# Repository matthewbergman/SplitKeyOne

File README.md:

# SplitKeyOne
Very simple split keyboard PCB layout and firmware using Cherry MX switches and Teensy3 micro.

### CAD
KiCAD pcb files

TODO:
* Fix the stabalizer mounting holes for vertically mounted keycaps
* Add more mounting holes for rigidity
* Switch to SMT diodes or switches with built in diodes

### SplitKeyOneFirmware
Simple firmware to read the key matrix and send the correct keypress or keyrelease signal. Optionally lights up the LED for each key while it is pressed.

TODO:
* Emulate mouse buttons
* Emulate joystick axis and buttons

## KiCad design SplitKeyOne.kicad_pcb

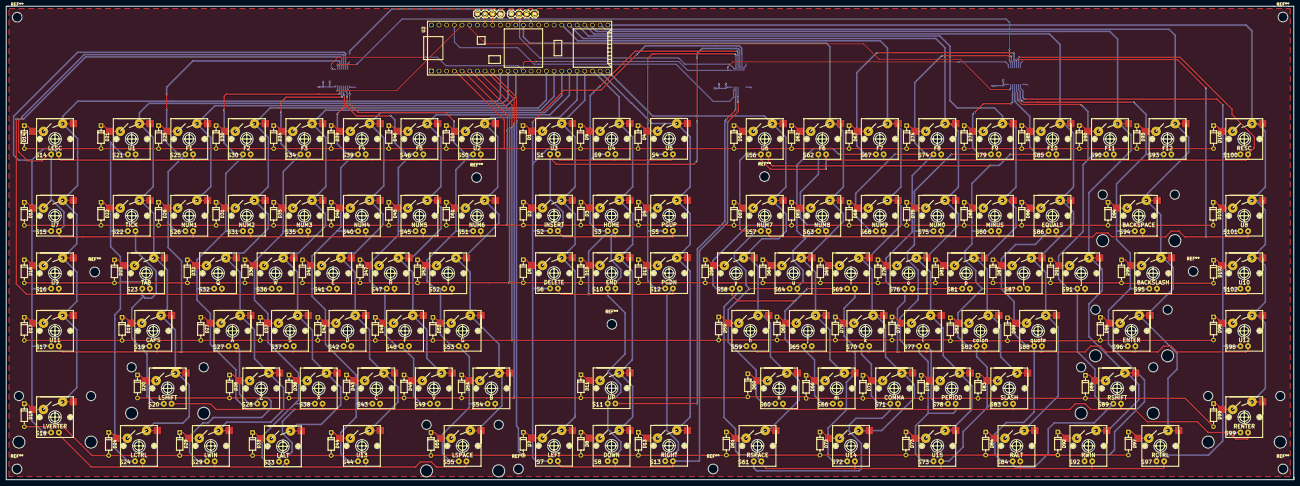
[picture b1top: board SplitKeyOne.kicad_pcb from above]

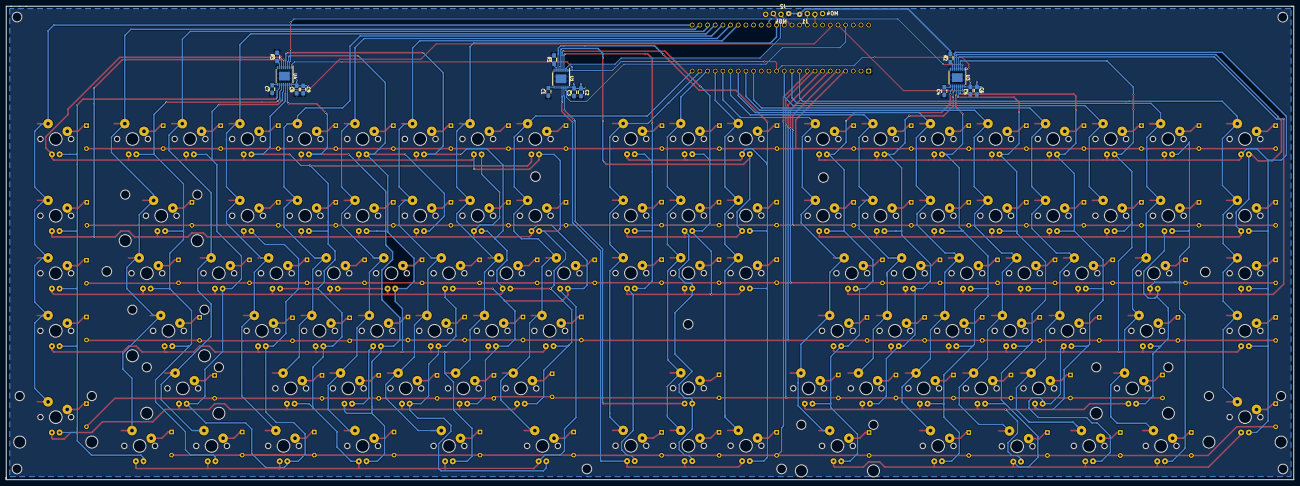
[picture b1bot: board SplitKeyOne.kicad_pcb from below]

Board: 2 copper layers, 426.2 x 156.7 mm, 222 parts (15 on the bottom side), 169 nets.

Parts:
C1, C4: 27pF; C_0805_HandSoldering
C2, C5, C8: 22uF; C_0805_HandSoldering
C3, C6, C9: 0.1uF; C_0805_HandSoldering
C7: C; C_0805_HandSoldering
D1, D2, D3, D4, D5, D6, D7, D8, D9, D10, D11, D12, D13, D14, D15, D16, D17, D18, D19, D20, D21, D22, D23, D24, D25, D26, D27, D28, D29, D30, D31, D32, D33, D34, D35, D36, D37, D38, D39, D40, D41, D42, D43, D44, D45, D46, D47, D48, D49, D50, D51, D52, D53, D54, D55, D56, D57, D58, D59, D60, D61, D62, D63, D64, D65, D66, D67, D68, D69, D70, D71, D72, D73, D74, D75, D76, D77, D78, D79, D80, D81, D82, D83, D84, D85, D86, D87, D88, D89, D90, D91, D92, D93, D94, D95, D96, D97, D98, D99, D100, D101, D102: D; D_DO-35_SOD27_P7.62mm_Horizontal
J1, J2: M04; SparkFun-1X04_LOCK
R1, R3: 56k; R_0805_HandSoldering
R2: 56K; R_0805_HandSoldering
S1: U3; CHERRY-MX-LED-Socket
S2: INSERT; CHERRY-MX-LED-Socket
S3: HOME; CHERRY-MX-LED-Socket
S4: U5; CHERRY-MX-LED-Socket
S5: PGUP; CHERRY-MX-LED-Socket
S6: DELETE; CHERRY-MX-LED-Socket
S7: LEFT; CHERRY-MX-LED-Socket
S8: DOWN; CHERRY-MX-LED-Socket
S9: U4; CHERRY-MX-LED-Socket
S10: END; CHERRY-MX-LED-Socket
S11: UP; CHERRY-MX-LED-Socket
S12: PGDN; CHERRY-MX-LED-Socket
S13: RIGHT; CHERRY-MX-LED-Socket
S14: LESC; CHERRY-MX-LED-Socket
S15: U7; CHERRY-MX-LED-Socket
S16: U9; CHERRY-MX-LED-Socket
S17: U11; CHERRY-MX-LED-Socket
S18: LVENTER; CHERRY-MX-LED-Socket-2-stabilizer
S19: CAPS; CHERRY-MX-LED-Socket
S20: LSHIFT; CHERRY-MX-LED-Socket-2-stabilizer
S21: U1; CHERRY-MX-LED-Socket
S22: TICK; CHERRY-MX-LED-Socket
S23: TAB; CHERRY-MX-LED-Socket
S24: LCTRL; CHERRY-MX-LED-Socket
S25: F1; CHERRY-MX-LED-Socket
S26: NUM1; CHERRY-MX-LED-Socket
S27: A; CHERRY-MX-LED-Socket
S28: Z; CHERRY-MX-LED-Socket
S29: LWIN; CHERRY-MX-LED-Socket
S30: F2; CHERRY-MX-LED-Socket
S31: NUM2; CHERRY-MX-LED-Socket
S32: Q; CHERRY-MX-LED-Socket
S33: LALT; CHERRY-MX-LED-Socket
S34: F3; CHERRY-MX-LED-Socket
S35: NUM3; CHERRY-MX-LED-Socket
S36: W; CHERRY-MX-LED-Socket
S37: S; CHERRY-MX-LED-Socket
S38: X; CHERRY-MX-LED-Socket
S39: F4; CHERRY-MX-LED-Socket
S40: NUM4; CHERRY-MX-LED-Socket
S41: E; CHERRY-MX-LED-Socket
S42: D; CHERRY-MX-LED-Socket
S43: C; CHERRY-MX-LED-Socket
S44: U13; CHERRY-MX-LED-Socket
S45: NUM5; CHERRY-MX-LED-Socket
S46: F5; CHERRY-MX-LED-Socket
S47: R; CHERRY-MX-LED-Socket
S48: F; CHERRY-MX-LED-Socket
S49: V; CHERRY-MX-LED-Socket
S50: U2; CHERRY-MX-LED-Socket
S51: NUM6; CHERRY-MX-LED-Socket
S52: T; CHERRY-MX-LED-Socket
S53: G; CHERRY-MX-LED-Socket
S54: B; CHERRY-MX-LED-Socket
S55: LSPACE; CHERRY-MX-LED-Socket-2-stabilizer
S56: U6; CHERRY-MX-LED-Socket
S57: NUM7; CHERRY-MX-LED-Socket
S58: y; CHERRY-MX-LED-Socket
S59: h; CHERRY-MX-LED-Socket
S60: n; CHERRY-MX-LED-Socket
S61: RSPACE; CHERRY-MX-LED-Socket
S62: F6; CHERRY-MX-LED-Socket
S63: NUM8; CHERRY-MX-LED-Socket
S64: u; CHERRY-MX-LED-Socket
S65: j; CHERRY-MX-LED-Socket
S66: m; CHERRY-MX-LED-Socket
S67: F7; CHERRY-MX-LED-Socket
S68: NUM9; CHERRY-MX-LED-Socket
S69: i; CHERRY-MX-LED-Socket
S70: k; CHERRY-MX-LED-Socket
S71: COMMA; CHERRY-MX-LED-Socket
S72: U14; CHERRY-MX-LED-Socket
S73: U15; CHERRY-MX-LED-Socket
S74: F8; CHERRY-MX-LED-Socket
S75: NUM0; CHERRY-MX-LED-Socket
S76: o; CHERRY-MX-LED-Socket
S77: l; CHERRY-MX-LED-Socket
S78: PERIOD; CHERRY-MX-LED-Socket
S79: F9; CHERRY-MX-LED-Socket
S80: MINUS; CHERRY-MX-LED-Socket
S81: p; CHERRY-MX-LED-Socket
S82: colon; CHERRY-MX-LED-Socket
S83: SLASH; CHERRY-MX-LED-Socket
S84: RALT; CHERRY-MX-LED-Socket
S85: F10; CHERRY-MX-LED-Socket
S86: EQUALS; CHERRY-MX-LED-Socket
S87: {; CHERRY-MX-LED-Socket
S88: quote; CHERRY-MX-LED-Socket
S89: RSHIFT; CHERRY-MX-LED-Socket-2-stabilizer
S90: F11; CHERRY-MX-LED-Socket
S91: ]; CHERRY-MX-LED-Socket
S92: RWIN; CHERRY-MX-LED-Socket
S93: F12; CHERRY-MX-LED-Socket
S94: BACKSPACE; CHERRY-MX-LED-Socket-2-stabilizer
S95: BACKSLASH; CHERRY-MX-LED-Socket
S96: ENTER; CHERRY-MX-LED-Socket-2-stabilizer
S97: RCTRL; CHERRY-MX-LED-Socket
S98: U12; CHERRY-MX-LED-Socket
S99: RENTER; CHERRY-MX-LED-Socket-2-stabilizer
S100: RESC; CHERRY-MX-LED-Socket
S101: U8; CHERRY-MX-LED-Socket
S102: U10; CHERRY-MX-LED-Socket
U1, U3, U4: MAX6951; TSSOP-16-1EP_4.4x5mm_Pitch0.65mm
U2: Teensy3.6_nopogo; Teensy35_36_nopogo

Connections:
5V: C2.1, C3.1, C5.1, C6.1, C8.1, C9.1, J1.4, J2.4, U1.16, U2.53, U3.16, U4.16
/C9: S1.S2, S2.S2, S6.S2, S7.S2, U2.21
/C10: S3.S2, S8.S2, S9.S2, S10.S2, S11.S2, U2.22
/C11: S4.S2, S5.S2, S12.S2, S13.S2, U2.23
/G15: J2.3, U2.42
/G16: J2.2, U2.43
/LED0: S1.K, S2.A, S4.K, S6.A, S7.A, S9.K, U1.6
/LED1: S1.A, S2.K, S3.K, S5.K, S8.A, S10.A, S11.A, U1.5
/LED2: S3.A, S6.K, S9.A, S10.K, S12.K, S13.A, U1.4
/LED3: S4.A, S5.A, S12.A, U1.3
/LED4: S11.K, U1.14
/LED5: S7.K, S8.K, S13.K, U1.13
/LED_CS1: U1.15, U2.50
/left/LED0: S14.K, S15.A, S16.A, S17.A, S18.A, S21.K, S25.K, S30.K, S34.K, S39.K, S46.K, S50.K, U3.6
/left/LED1: S14.A, S15.K, S19.A, S20.A, S22.K, S23.A, S26.K, S31.K, S35.K, S40.K, S45.K, S51.K, U3.5
/left/LED2: S16.K, S21.A, S22.A, S23.K, S24.A, S32.K, S36.K, S41.K, S47.K, S52.K, U3.4
/left/LED3: S17.K, S19.K, S25.A, S26.A, S27.K, S28.A, S29.A, S37.K, S42.K, S48.K, S53.K, U3.3
/left/LED4: S20.K, S27.A, S28.K, S30.A, S31.A, S32.A, S33.A, S38.K, S43.K, S49.K, S54.K, U3.14
/left/LED5: S18.K, S24.K, S29.K, S33.K, S34.A, S35.A, S36.A, S37.A, S38.A, S44.K, S55.K, U3.13
/left/LED6: S39.A, S40.A, S41.A, S42.A, S43.A, S44.A, U3.12
/left/LED7: S45.A, S46.A, S47.A, S48.A, S49.A, U3.11
/left/LED8: S50.A, S51.A, S52.A, S53.A, S54.A, S55.A, U3.10
/right/LED0: S56.A, S57.A, S59.A, S60.A, S62.K, S64.A, S67.K, S74.K, S79.K, S85.K, S90.K, S93.K, S100.K, U4.6
/right/LED1: S57.K, S58.A, S62.A, S63.K, S65.A, S66.A, S68.K, S69.A, S75.K, S80.K, S86.K, S94.K, S101.K, U4.5
/right/LED2: S61.A, S63.A, S64.K, S67.A, S69.K, S70.A, S71.A, S76.K, S81.K, S87.K, S91.K, S95.K, S102.K, U4.4
/right/LED3: S59.K, S65.K, S68.A, S70.K, S72.A, S74.A, S76.A, S77.K, S78.A, S82.K, S88.K, S96.K, S98.K, U4.3
/right/LED4: S60.K, S66.K, S71.K, S73.A, S75.A, S77.A, S78.K, S79.A, S81.A, S83.K, S89.K, S99.K, U4.14
/right/LED5: S56.K, S58.K, S61.K, S72.K, S73.K, S80.A, S82.A, S83.A, S84.K, S85.A, S87.A, S92.K, S97.K, U4.13
/right/LED6: S84.A, S86.A, S88.A, S89.A, S90.A, S91.A, U4.12
/right/LED7: S92.A, S93.A, S94.A, S95.A, S96.A, U4.11
/right/LED8: S97.A, S98.A, S99.A, S100.A, S101.A, S102.A, U4.10
C1: S14.S2, S15.S2, S16.S2, S17.S2, S18.S2, U2.10
C2: S19.S2, S20.S2, S21.S2, S22.S2, S23.S2, S24.S2, U2.11
C3: S25.S2, S26.S2, U2.12
C4: S27.S2, S28.S2, S29.S2, S30.S2, S31.S2, S32.S2, U2.16
C5: S33.S2, S34.S2, S35.S2, S36.S2, S37.S2, S38.S2, U2.17
C6: S39.S2, S40.S2, S41.S2, S42.S2, S43.S2, S44.S2, U2.18
C7: S45.S2, S46.S2, S47.S2, S48.S2, S49.S2, U2.19
C8: S50.S2, S51.S2, S52.S2, S53.S2, S54.S2, S55.S2, U2.20
C12: S56.S2, S57.S2, S58.S2, S59.S2, S60.S2, S61.S2, U2.24
C13: S62.S2, S63.S2, S64.S2, S65.S2, S66.S2, U2.41
C14: S67.S2, S68.S2, S69.S2, S70.S2, S71.S2, S72.S2, U2.36
C15: S73.S2, S74.S2, S75.S2, S76.S2, S77.S2, S78.S2, U2.35
C16: S79.S2, S80.S2, S81.S2, S82.S2, S83.S2, U2.34
C17: S84.S2, S85.S2, S86.S2, S87.S2, S88.S2, U2.33
C18: S89.S2, S90.S2, S91.S2, S92.S2, U2.32
C19: S93.S2, S94.S2, S95.S2, S96.S2, S97.S2, U2.31
C20: S98.S2, S99.S2, S100.S2, S101.S2, S102.S2, U2.30
GND: C1.2, C2.2, C3.2, C4.2, C5.2, C6.2, C7.2, C8.2, C9.2, J1.1, J2.1, R1.2, R2.2, R3.2, U1.8, U1.17, U2.1, U3.8, U3.17, U4.8, U4.17
LED_CS2: U2.49, U3.15
LED_CS3: U2.48, U4.15
MOSI: U1.1, U2.13, U3.1, U4.1
unnamed: C1.1, U1.9
unnamed: C4.1, U3.9
unnamed: C7.1, U4.9
unnamed: D1.1, S1.S1
unnamed: D2.1, S2.S1
unnamed: D3.1, S3.S1
unnamed: D4.1, S4.S1
unnamed: D5.1, S5.S1
unnamed: D6.1, S6.S1
unnamed: D7.1, S7.S1
unnamed: D8.1, S8.S1
unnamed: D9.1, S9.S1
unnamed: D10.1, S10.S1
unnamed: D11.1, S11.S1
unnamed: D12.1, S12.S1
unnamed: D13.1, S13.S1
unnamed: D14.1, S14.S1
unnamed: D15.1, S15.S1
unnamed: D16.1, S16.S1
unnamed: D17.1, S17.S1
unnamed: D18.1, S18.S1
unnamed: D19.1, S19.S1
unnamed: D20.1, S20.S1
unnamed: D21.1, S21.S1
unnamed: D22.1, S22.S1
unnamed: D23.1, S23.S1
unnamed: D24.1, S24.S1
unnamed: D25.1, S25.S1
unnamed: D26.1, S26.S1
unnamed: D27.1, S27.S1
unnamed: D28.1, S28.S1
unnamed: D29.1, S29.S1
unnamed: D30.1, S30.S1
unnamed: D31.1, S31.S1
unnamed: D32.1, S32.S1
unnamed: D33.1, S33.S1
unnamed: D34.1, S34.S1
unnamed: D35.1, S35.S1
unnamed: D36.1, S36.S1
unnamed: D37.1, S37.S1
unnamed: D38.1, S38.S1
unnamed: D39.1, S39.S1
unnamed: D40.1, S40.S1
unnamed: D41.1, S41.S1
unnamed: D42.1, S42.S1
unnamed: D43.1, S43.S1
unnamed: D44.1, S44.S1
unnamed: D45.1, S45.S1
unnamed: D46.1, S46.S1
unnamed: D47.1, S47.S1
unnamed: D48.1, S48.S1
unnamed: D49.1, S49.S1
unnamed: D50.1, S50.S1
unnamed: D51.1, S51.S1
unnamed: D52.1, S52.S1
unnamed: D53.1, S53.S1
unnamed: D54.1, S54.S1
unnamed: D55.1, S55.S1
unnamed: D56.1, S56.S1
unnamed: D57.1, S57.S1
unnamed: D58.1, S58.S1
unnamed: D59.1, S59.S1
unnamed: D60.1, S60.S1
unnamed: D61.1, S61.S1
unnamed: D62.1, S62.S1
unnamed: D63.1, S63.S1
unnamed: D64.1, S64.S1
unnamed: D65.1, S65.S1
unnamed: D66.1, S66.S1
unnamed: D67.1, S67.S1
unnamed: D68.1, S68.S1
unnamed: D69.1, S69.S1
unnamed: D70.1, S70.S1
unnamed: D71.1, S71.S1
unnamed: D72.1, S72.S1
unnamed: D73.1, S73.S1
unnamed: D74.1, S74.S1
unnamed: D75.1, S75.S1
unnamed: D76.1, S76.S1
unnamed: D77.1, S77.S1
unnamed: D78.1, S78.S1
unnamed: D79.1, S79.S1
unnamed: D80.1, S80.S1
unnamed: D81.1, S81.S1
unnamed: D82.1, S82.S1
unnamed: D83.1, S83.S1
unnamed: D84.1, S84.S1
unnamed: D85.1, S85.S1
unnamed: D86.1, S86.S1
unnamed: D87.1, S87.S1
unnamed: D88.1, S88.S1
unnamed: D89.1, S89.S1
unnamed: D90.1, S90.S1
unnamed: D91.1, S91.S1
unnamed: D92.1, S92.S1
unnamed: D93.1, S93.S1
unnamed: D94.1, S94.S1
unnamed: D95.1, S95.S1
unnamed: D96.1, S96.S1
unnamed: D97.1, S97.S1
unnamed: D98.1, S98.S1
unnamed: D99.1, S99.S1
unnamed: D100.1, S100.S1
unnamed: D101.1, S101.S1
unnamed: D102.1, S102.S1
unnamed: R1.1, U1.7
unnamed: R2.1, U3.7
unnamed: R3.1, U4.7
R1: D1.2, D4.2, D9.2, D14.2, D21.2, D25.2, D30.2, D34.2, D39.2, D46.2, D50.2, D56.2, D62.2, D67.2, D74.2, D79.2, D85.2, D90.2, D93.2, D100.2, U2.4
R2: D2.2, D3.2, D5.2, D15.2, D22.2, D26.2, D31.2, D35.2, D40.2, D45.2, D51.2, D57.2, D63.2, D68.2, D75.2, D80.2, D86.2, D94.2, D101.2, U2.5
R3: D6.2, D10.2, D12.2, D16.2, D23.2, D32.2, D36.2, D41.2, D47.2, D52.2, D58.2, D64.2, D69.2, D76.2, D81.2, D87.2, D91.2, D95.2, D102.2, U2.6
R4: D17.2, D19.2, D27.2, D37.2, D42.2, D48.2, D53.2, D59.2, D65.2, D70.2, D77.2, D82.2, D88.2, D96.2, D98.2, U2.7
R5: D11.2, D20.2, D28.2, D38.2, D43.2, D49.2, D54.2, D60.2, D66.2, D71.2, D78.2, D83.2, D89.2, D99.2, U2.8
R6: D7.2, D8.2, D13.2, D18.2, D24.2, D29.2, D33.2, D44.2, D55.2, D61.2, D72.2, D73.2, D84.2, D92.2, D97.2, U2.9
SCK: U1.2, U2.40, U3.2, U4.2
SCL: J1.3, U2.46
SDA: J1.2, U2.45

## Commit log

2018-10-15 Initial commit.
2018-10-15 Rough layout of right side.
2018-10-18 Added libs.
2018-10-18 Hopefully final layout of keys.
2018-10-18 Final key placement.
2018-10-19 More routing.
2018-10-19 Board routed.
2018-10-20 Mounting holes.
2018-10-27 Making outlines for routing the plate.
2018-10-27 Moving KiCAD to CAD folder.
2018-10-27 Adding firmware.
2018-11-02 LED code
2018-11-03 Work on the right side keys.
2018-11-06 keymap.
2020-01-07 Cleaned up files
2020-01-07 Added image
